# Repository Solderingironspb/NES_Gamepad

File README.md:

# NES_Gamepad
## Подключаем геймпад от NES к STM32F103C8T6

##### P.S. Для новичков в программировании - готовые прошивки 100% заведутся на МК STM32F103C8T6, STM32F103CBT6, GD32F103CBT6, CH32F103C8T6. Протестировано лично. Воспользуйтесь программой STM32 ST-Link Utility. Подключитесь программатором к плате. Очистите МК. Откройте файл прошивки из папки с готовыми прошивками, например "NES Controller 1.bin" и залейте ее на МК. Target -> Program & Verify Ctrl + P -> Start.

**[[Смотреть видео]](https://youtu.be/_236TtiKs34)**
**[[Главная страница]](https://github.com/Solderingironspb/Lessons-Stm32/blob/master/README.md)**

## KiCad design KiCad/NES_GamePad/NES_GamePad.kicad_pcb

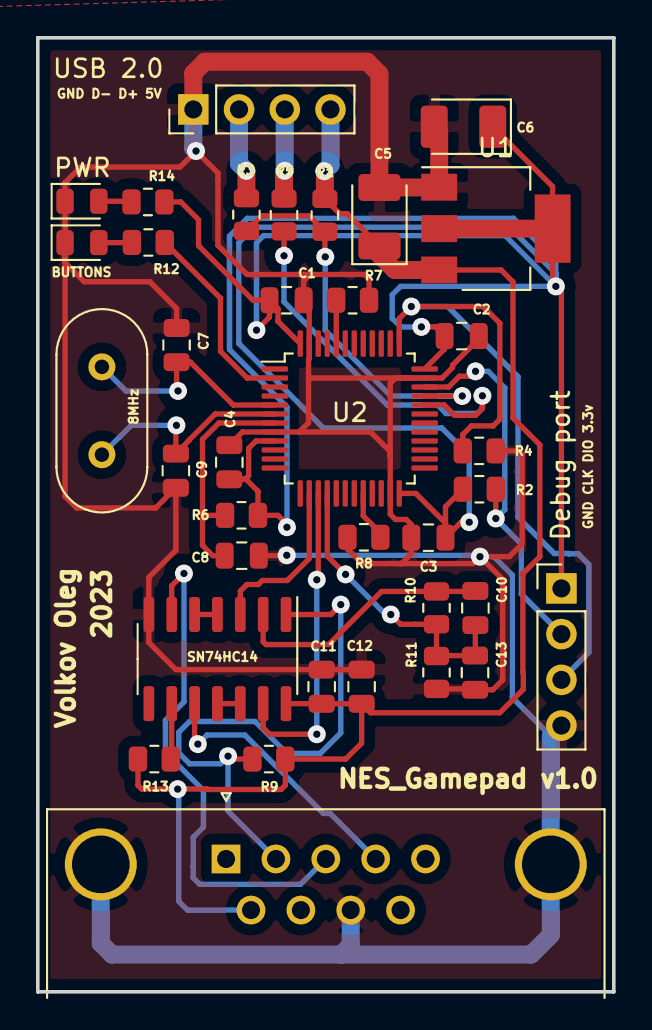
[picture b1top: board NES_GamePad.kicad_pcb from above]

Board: 2 copper layers, 32.0 x 53.0 mm, 36 parts (0 on the bottom side), 27 nets.

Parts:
8MHz: 8MHz; Crystal_HC49-U_Vertical
BUTTONS: LED; LED_0805_2012Metric
C1, C2, C3, C4, C8, C11: 0.1uF; C_0805_2012Metric
C5, C6: 47uF; CP_EIA-3528-21_Kemet-B_Pad1.50x2.35mm_HandSolder
C7, C9: 30pF; C_0805_2012Metric
C10: 150p; C_0805_2012Metric
C12: 10uF; C_0805_2012Metric
C13: 30p; C_0805_2012Metric
Debug port: Serial wire; PinHeader_1x04_P2.54mm_Vertical
NES_Gamepad v1.0: NES; DSUB-9_Male_Horizontal_P2.77x2.84mm_EdgePinOffset4.94mm_Hou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
PWR: LED; LED_0805_2012Metric
R1, R2, R4, R6, R7, R8, R13: 10k; R_0805_2012Metric
R3, R5: 20; R_0805_2012Metric
R9: 100k; R_0805_2012Metric
R10: 390; R_0805_2012Metric
R11: 680; R_0805_2012Metric
R12, R14: 1k; R_0805_2012Metric
SN74HC14: 74HC14; SOIC-14_3.9x8.7mm_P1.27mm
U1: AMS1117-3.3; SOT-223-3_TabPin2
U2: STM32F103C8Tx; LQFP-48_7x7mm_P0.5mm
USB 2.0: Serial wire; PinHeader_1x04_P2.54mm_Vertical

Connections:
3.3V: C1.1, C2.1, C3.1, C4.1, C6.1, Debug port.1, R2.2, R6.2, R14.1, U1.2, U2.9, U2.24, U2.36, U2.48
5V: C5.1, C11.1, C12.1, NES_Gamepad v1.0.6, R1.2, R9.2, R13.1, SN74HC14.14, U1.3, USB 2.0.4
BOOT0: R7.2, U2.44
BOOT1: R8.2, U2.20
GND: BUTTONS.1, C1.2, C2.2, C3.2, C4.2, C5.2, C6.2, C7.1, C8.2, C9.1, C11.2, C12.2, C13.2, Debug port.4, NES_Gamepad v1.0.0, NES_Gamepad v1.0.8, PWR.1, R4.1, R7.1, R8.1, R11.1, SN74HC14.7, U1.1, U2.8, U2.23, U2.35, U2.47, USB 2.0.1
LED: R12.1, U2.2
NRST: C8.1, R6.1, U2.7
unnamed: C10.1, R10.2, SN74HC14.2
unnamed: BUTTONS.2, R12.2
unnamed: PWR.2, R14.2
unnamed: R5.2, USB 2.0.3
unnamed: R3.2, USB 2.0.2
unnamed: NES_Gamepad v1.0.2, R9.1, SN74HC14.1
unnamed: NES_Gamepad v1.0.3, SN74HC14.6
unnamed: NES_Gamepad v1.0.4, SN74HC14.10
unnamed: R13.2, SN74HC14.9
unnamed: SN74HC14.4, SN74HC14.5
unnamed: SN74HC14.11, SN74HC14.12
PA4: SN74HC14.3, U2.14
PA5: SN74HC14.13, U2.15
PA6: C10.2, C13.1, R10.1, R11.2, U2.16
PA11: R5.1, U2.32
PA12: R1.1, R3.1, U2.33
PA13: Debug port.2, R2.1, U2.34
PA14: Debug port.3, R4.2, U2.37
PD0: 8MHz.1, C7.2, U2.5
PD1: 8MHz.2, C9.2, U2.6

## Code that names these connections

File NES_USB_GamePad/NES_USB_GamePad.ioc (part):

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Mcu.Name=STM32F103C(8-B)Tx
Mcu.Package=LQFP48
Mcu.UserName=STM32F103C8Tx
PA11.Mode=Device
PA11.Signal=USB_DM
PA12.Mode=Device
PA12.Signal=USB_DP
PA13.Mode=Serial_Wire
PA13.Signal=SYS_JTMS-SWDIO
PA14.Mode=Serial_Wire
PA14.Signal=SYS_JTCK-SWCLK
PD0-OSC_IN.Mode=HSE-External-Oscillator
PD0-OSC_IN.Signal=RCC_OSC_IN
PD1-OSC_OUT.Mode=HSE-External-Oscillator
PD1-OSC_OUT.Signal=RCC_OSC_OUT
RCC.SYSCLKFreq_VALUE=72000000
RCC.SYSCLKSource=RCC_SYSCLKSOURCE_PLLCLK
board=custom

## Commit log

2023-02-09 USB GamePad
2023-02-25 26.02.2023 - 3D, KiCad, code
2023-03-14 14.03.2023 - Добавлены готовые прошивки. Сделан релиз
